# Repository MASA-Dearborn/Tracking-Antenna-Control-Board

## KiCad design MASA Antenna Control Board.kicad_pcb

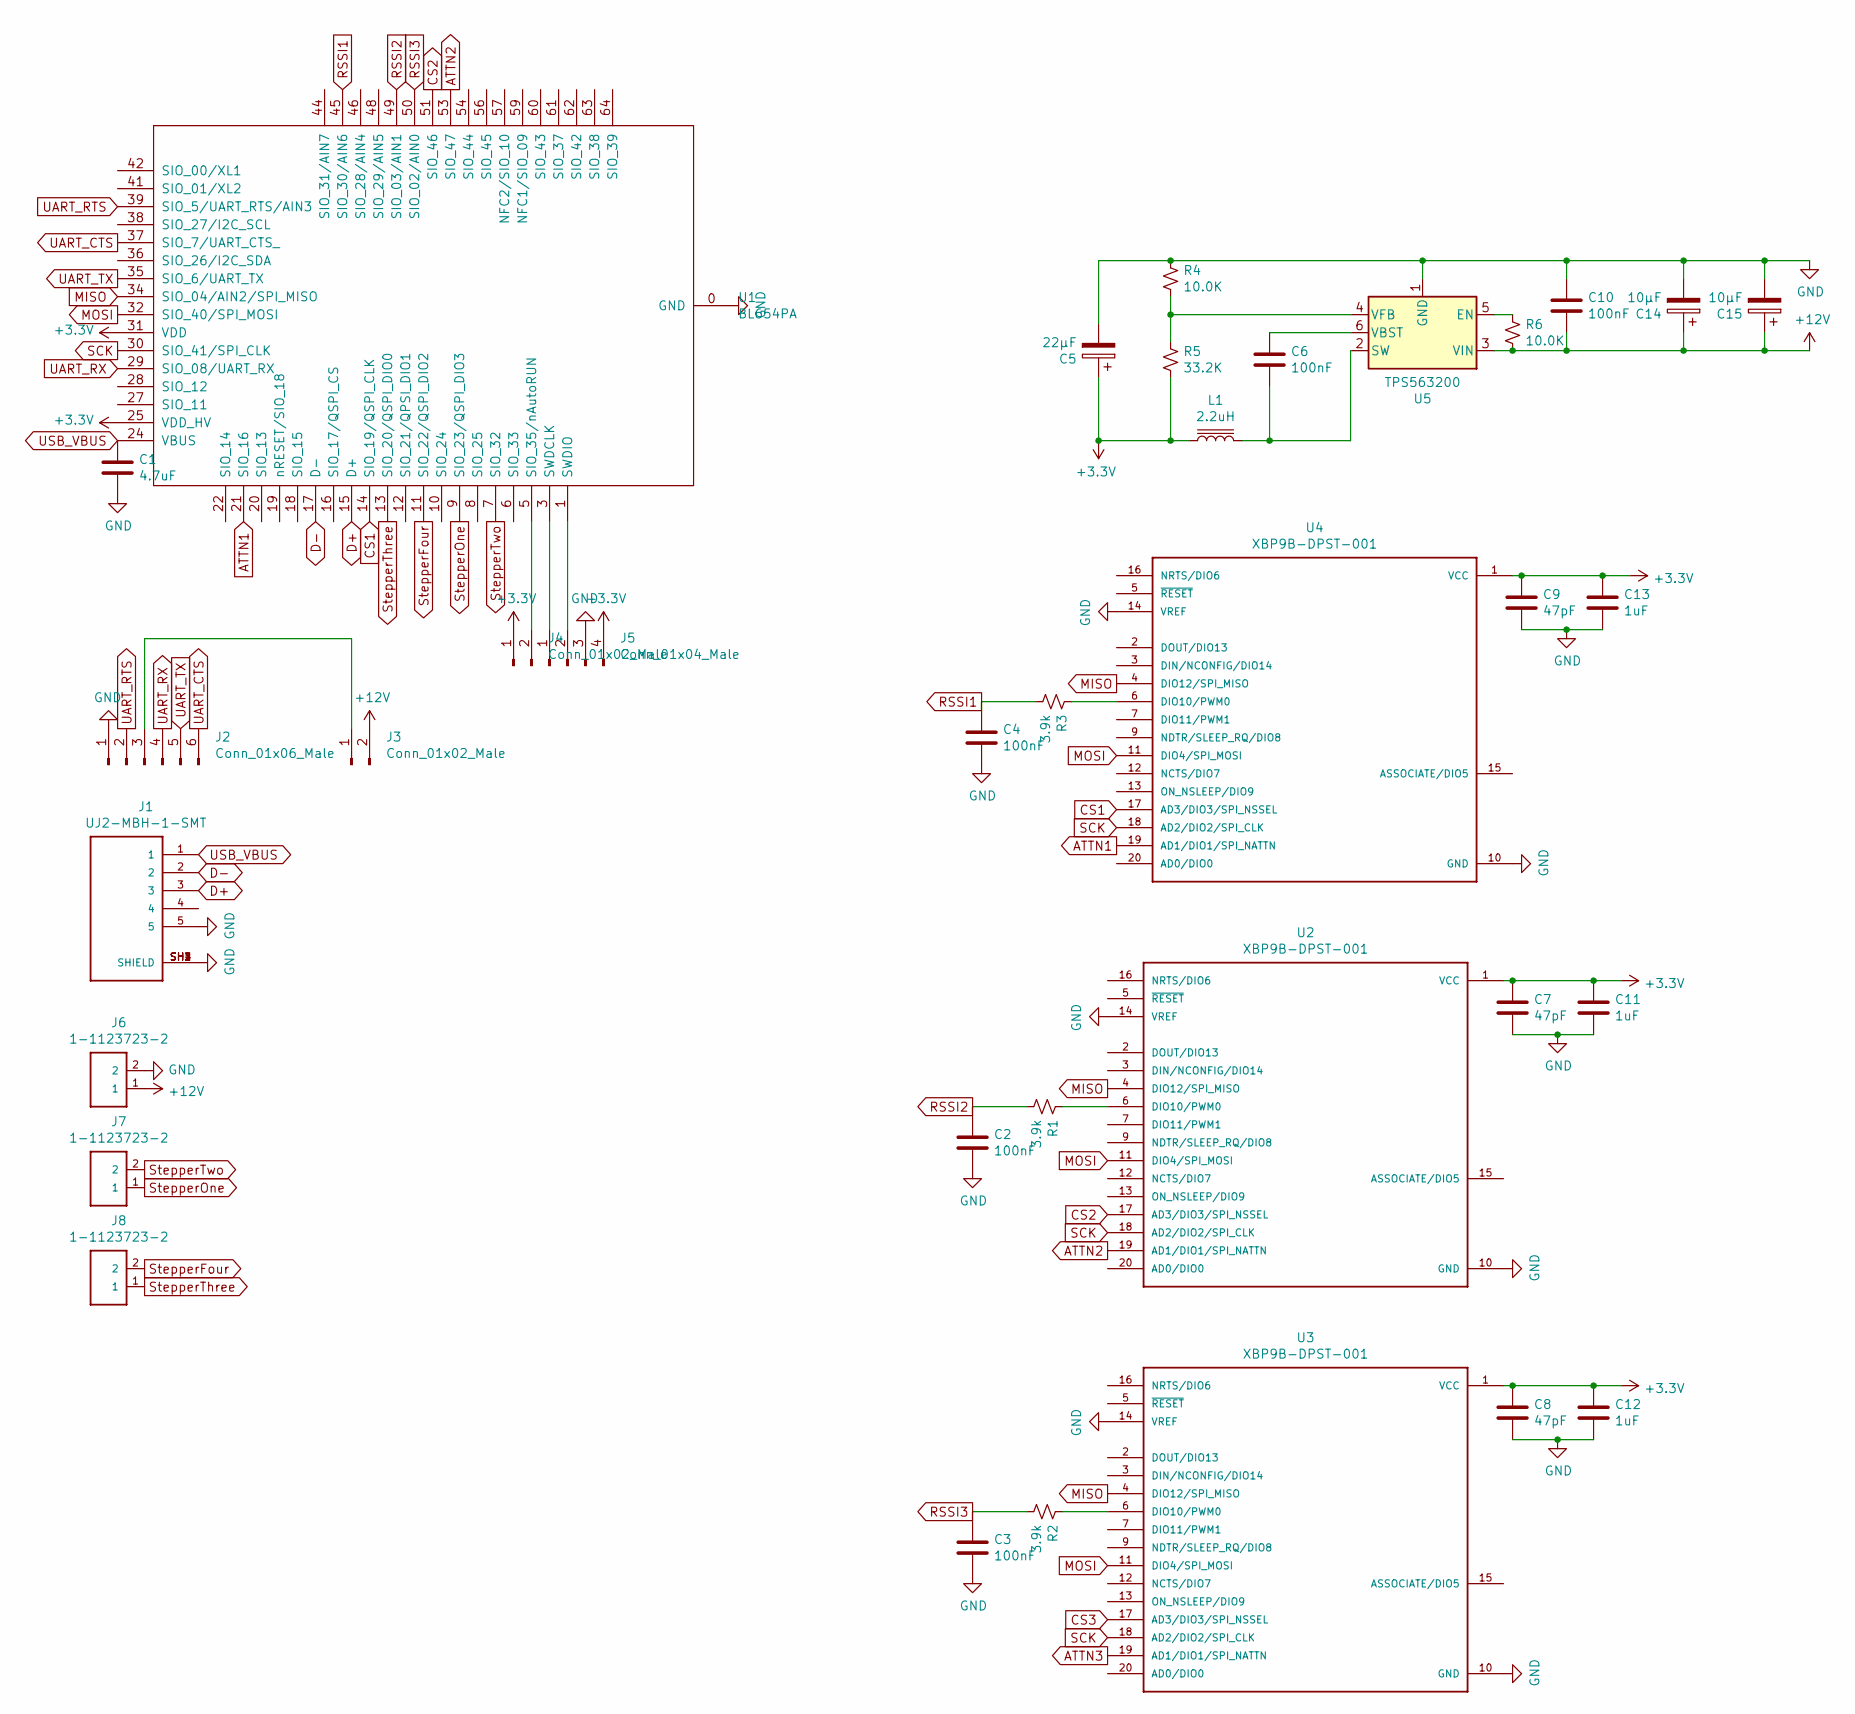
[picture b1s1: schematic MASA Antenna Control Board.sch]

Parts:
C1: 4.7uF; C_0805_2012Metric
C2, C3, C4, C6, C10: 100nF; C_0805_2012Metric
C5: 22μF; CP_Radial_D5.0mm_P2.00mm
C7, C8, C9: 47pF; C_0805_2012Metric
C11, C12, C13: 1uF; C_0805_2012Metric
C14, C15: 10μF; CP_Radial_D5.0mm_P2.00mm
J1: UJ2-MBH-1-SMT; CUI_UJ2-MBH-1-SMT
J2: Conn_01x06_Male; PinSocket_1x06_P2.54mm_Vertical
J3, J4: Conn_01x02_Male; PinSocket_1x02_P2.54mm_Vertical
J5: Conn_01x04_Male; PinSocket_1x04_P2.54mm_Vertical
J6, J7, J8: 1-1123723-2; TE_1-1123723-2
L1: 2.2uH; L_0805_2012Metric
R1, R2, R3: 3.9k; R_0805_2012Metric
R4, R6: 10.0K; R_0805_2012Metric
R5: 33.2K; R_0805_2012Metric
U1: BL654PA
U2, U3, U4: XBP9B-DPST-001; DIP2200W51P200L3294H279Q20P
U5: TPS563200; SOT-23-6

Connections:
+3V3: C5.1, C7.1, C8.1, C9.1, C11.1, C12.1, C13.1, J4.1, J5.4, L1.1, R5.2, U1.25 (VDD_HV), U1.31 (VDD), U2.1 (VCC), U3.1 (VCC), U4.1 (VCC)
+12V: C10.2, C14.1, C15.1, J3.2, J6.1, R6.2, U5.3 (VIN)
ATTN1: U1.21 (SIO_16), U4.19 (AD1/DIO1/SPI_NATTN)
ATTN2: U1.53 (SIO_47), U2.19 (AD1/DIO1/SPI_NATTN)
ATTN3: U3.19 (AD1/DIO1/SPI_NATTN)
CS1: U1.14 (SIO_19/QSPI_CLK), U4.17 (AD3/DIO3/SPI_NSSEL)
CS2: U1.51 (SIO_46), U2.17 (AD3/DIO3/SPI_NSSEL)
CS3: U3.17 (AD3/DIO3/SPI_NSSEL)
D+: J1.3, U1.15 (D+)
D-: J1.2, U1.17 (D-)
GND: C1.2, C2.2, C3.2, C4.2, C5.2, C7.2, C8.2, C9.2, C10.1, C11.2, C12.2, C13.2, C14.2, C15.2, J1.5, J1.SH1 (SHIELD), J1.SH2 (SHIELD), J1.SH3 (SHIELD), J1.SH4 (SHIELD), J2.1, J5.3, J6.2, R4.1, U1.0 (GND), U1.23 (GND), U1.26 (GND), U1.33 (GND), U1.40 (GND), U1.43 (GND), U1.47 (GND), U1.52 (GND), U1.55 (GND), U1.58 (GND), U1.65 (GND), U1.66 (GND), U1.67 (GND), U1.68 (GND), U1.69 (GND), U1.70 (GND), U1.71 (GND), U1.72 (GND), U1.73 (GND), U1.74 (GND), U1.75 (GND), U1.76 (GND), U1.77 (GND), U1.78 (GND), U1.79 (GND), U2.10 (GND), U2.14 (VREF), U3.10 (GND), U3.14 (VREF), U4.10 (GND), U4.14 (VREF), U5.1 (GND)
MISO: U1.34 (SIO_04/AIN2/SPI_MISO), U2.4 (DIO12/SPI_MISO), U3.4 (DIO12/SPI_MISO), U4.4 (DIO12/SPI_MISO)
MOSI: U1.32 (SIO_40/SPI_MOSI), U2.11 (DIO4/SPI_MOSI), U3.11 (DIO4/SPI_MOSI), U4.11 (DIO4/SPI_MOSI)
unnamed: C6.1, U5.6 (VBST)
unnamed: C6.2, L1.2, U5.2 (SW)
unnamed: J2.3, J3.1
unnamed: J4.2, U1.5 (SIO_35/nAutoRUN)
unnamed: J5.1, U1.3 (SWDCLK)
unnamed: J5.2, U1.1 (SWDIO)
unnamed: R1.1, U2.6 (DIO10/PWM0)
unnamed: R2.1, U3.6 (DIO10/PWM0)
unnamed: R3.1, U4.6 (DIO10/PWM0)
unnamed: R4.2, R5.1, U5.4 (VFB)
unnamed: R6.1, U5.5 (EN)
RSSI1: C4.1, R3.2, U1.45 (SIO_30/AIN6)
RSSI2: C2.1, R1.2, U1.49 (SIO_03/AIN1)
RSSI3: C3.1, R2.2, U1.50 (SIO_02/AIN0)
SCK: U1.30 (SIO_41/SPI_CLK), U2.18 (AD2/DIO2/SPI_CLK), U3.18 (AD2/DIO2/SPI_CLK), U4.18 (AD2/DIO2/SPI_CLK)
StepperFour: J8.2, U1.11 (SIO_22/QSPI_DIO2)
StepperOne: J7.1, U1.9 (SIO_23/QSPI_DIO3)
StepperThree: J8.1, U1.13 (SIO_20/QSPI_DIO0)
StepperTwo: J7.2, U1.7 (SIO_32)
UART_CTS: J2.6, U1.37 (SIO_7/UART_CTS_)
UART_RTS: J2.2, U1.39 (SIO_5/UART_RTS/AIN3)
UART_RX: J2.4, U1.29 (SIO_08/UART_RX)
UART_TX: J2.5, U1.35 (SIO_6/UART_TX)
USB_VBUS: C1.1, J1.1, U1.24 (VBUS)

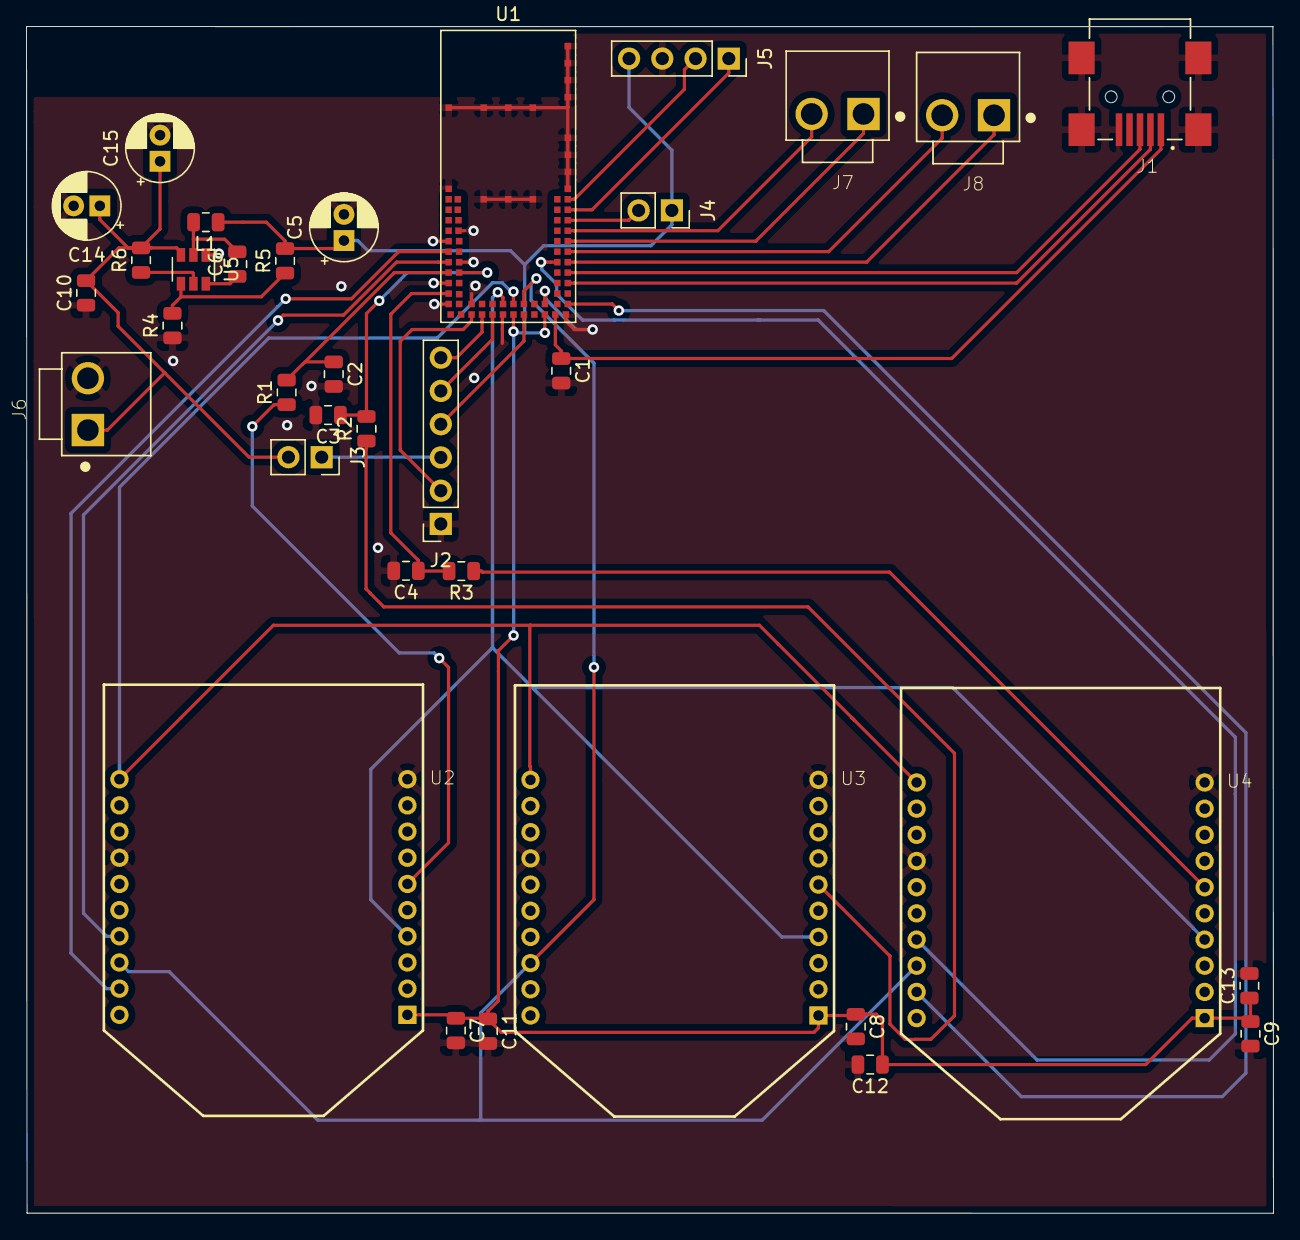
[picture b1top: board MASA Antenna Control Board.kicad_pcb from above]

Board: 2 copper layers, 95.3 x 90.7 mm, 35 parts (0 on the bottom side), 35 nets.

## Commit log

2020-01-19 Finished schematic and assigned footprints
2020-01-20 Finished most routing
2020-02-25 Finished routing
